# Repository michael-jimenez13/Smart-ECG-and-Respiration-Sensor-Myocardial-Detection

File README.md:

# Smart-ECG-and-Respiration-Sensor-Myocardial-Detection

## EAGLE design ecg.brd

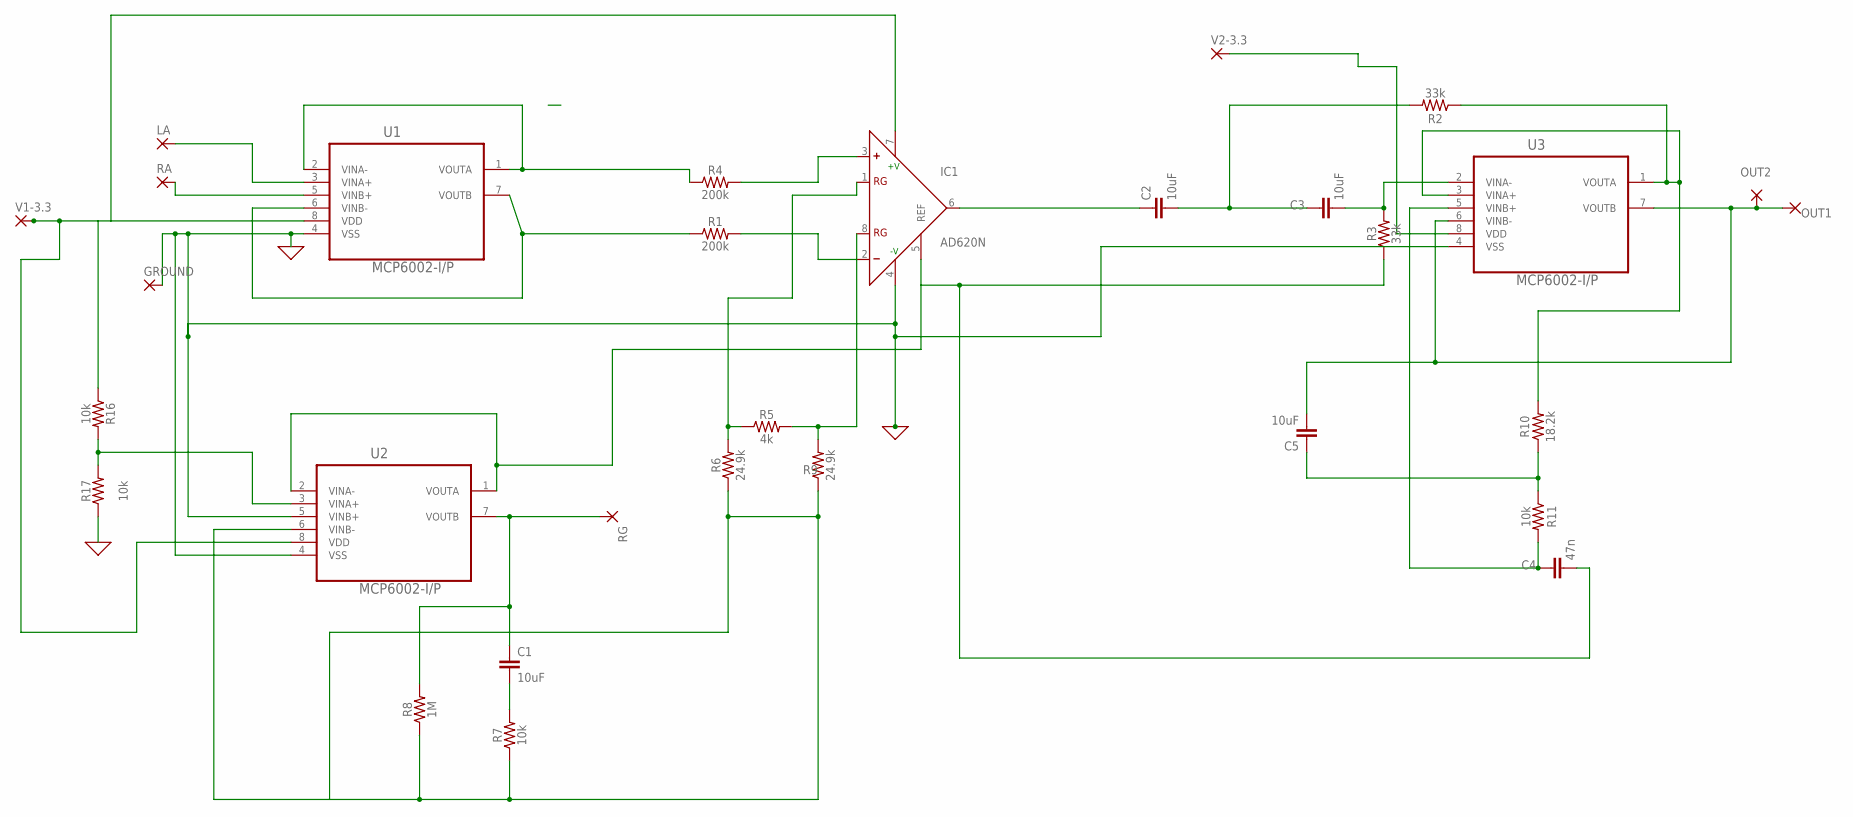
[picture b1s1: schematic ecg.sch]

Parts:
C1, C2, C3, C5: 10uF; CAP-PTH-SMALL-KIT
C4: 47n; CAP-PTH-SMALL-KIT
GROUND: 3,81/1,4
IC1: AD620N; DIL08
LA: 3,81/1,4
OUT1, OUT2: 3,81/1,4
R1, R4: 200k; AXIAL-0.3
R2, R3: 33k; AXIAL-0.3
R5: 4k; AXIAL-0.3
R6, R9: 24.9k; AXIAL-0.3
R7, R11, R16, R17: 10k; AXIAL-0.3
R8: 1M; AXIAL-0.3
R10: 18.2k; AXIAL-0.3
RA: 3,81/1,4
RG: 3,81/1,4
U1, U2, U3: MCP6002-I/P; DIP254P762X533-8
V1-3.3, V2-3.3: 3,81/1,4

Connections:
0: GROUND.1, IC1.4 (-V), R17.P$1 (1), U1.4 (VSS), U2.4 (VSS), U2.5 (VINB+), U3.4 (VSS)
unnamed: R6.P$1 (1), R7.P$1 (1), R8.P$1 (1), R9.P$1 (1), U2.6 (VINB-)
unnamed: IC1.7 (+V), R16.P$1 (1), U1.8 (VDD), U2.8 (VDD), V1-3.3.1
unnamed: C1.2, R7.P$2 (2)
unnamed: C4.2, IC1.5 (REF), R3.P$1 (1), U2.1 (VOUTA), U2.2 (VINA-)
unnamed: R16.P$2 (2), R17.P$2 (2), U2.3 (VINA+)
unnamed: R2.P$1 (1), R10.P$2 (2), U3.1 (VOUTA), U3.3 (VINA+)
unnamed: LA.1, U1.3 (VINA+)
unnamed: RA.1, U1.5 (VINB+)
unnamed: R1.P$1 (1), U1.6 (VINB-), U1.7 (VOUTB)
unnamed: R4.P$1 (1), U1.1 (VOUTA), U1.2 (VINA-)
unnamed: IC1.3 (+), R4.P$2 (2)
unnamed: U3.8 (VDD), V2-3.3.1
unnamed: C2.2, C3.1, R2.P$2 (2)
unnamed: C2.1, IC1.6 (OUT)
unnamed: C3.2, R3.P$2 (2), U3.2 (VINA-)
unnamed: C5.1, R10.P$1 (1), R11.P$1 (1)
unnamed: C4.1, R11.P$2 (2), U3.5 (VINB+)
unnamed: C5.2, OUT1.1, OUT2.1, U3.6 (VINB-), U3.7 (VOUTB)
unnamed: IC1.2 (-), R1.P$2 (2)
unnamed: C1.1, R8.P$2 (2), RG.1, U2.7 (VOUTB)
unnamed: IC1.1 (RG), R5.P$1 (1), R6.P$2 (2)
unnamed: IC1.8 (RG), R5.P$2 (2), R9.P$2 (2)

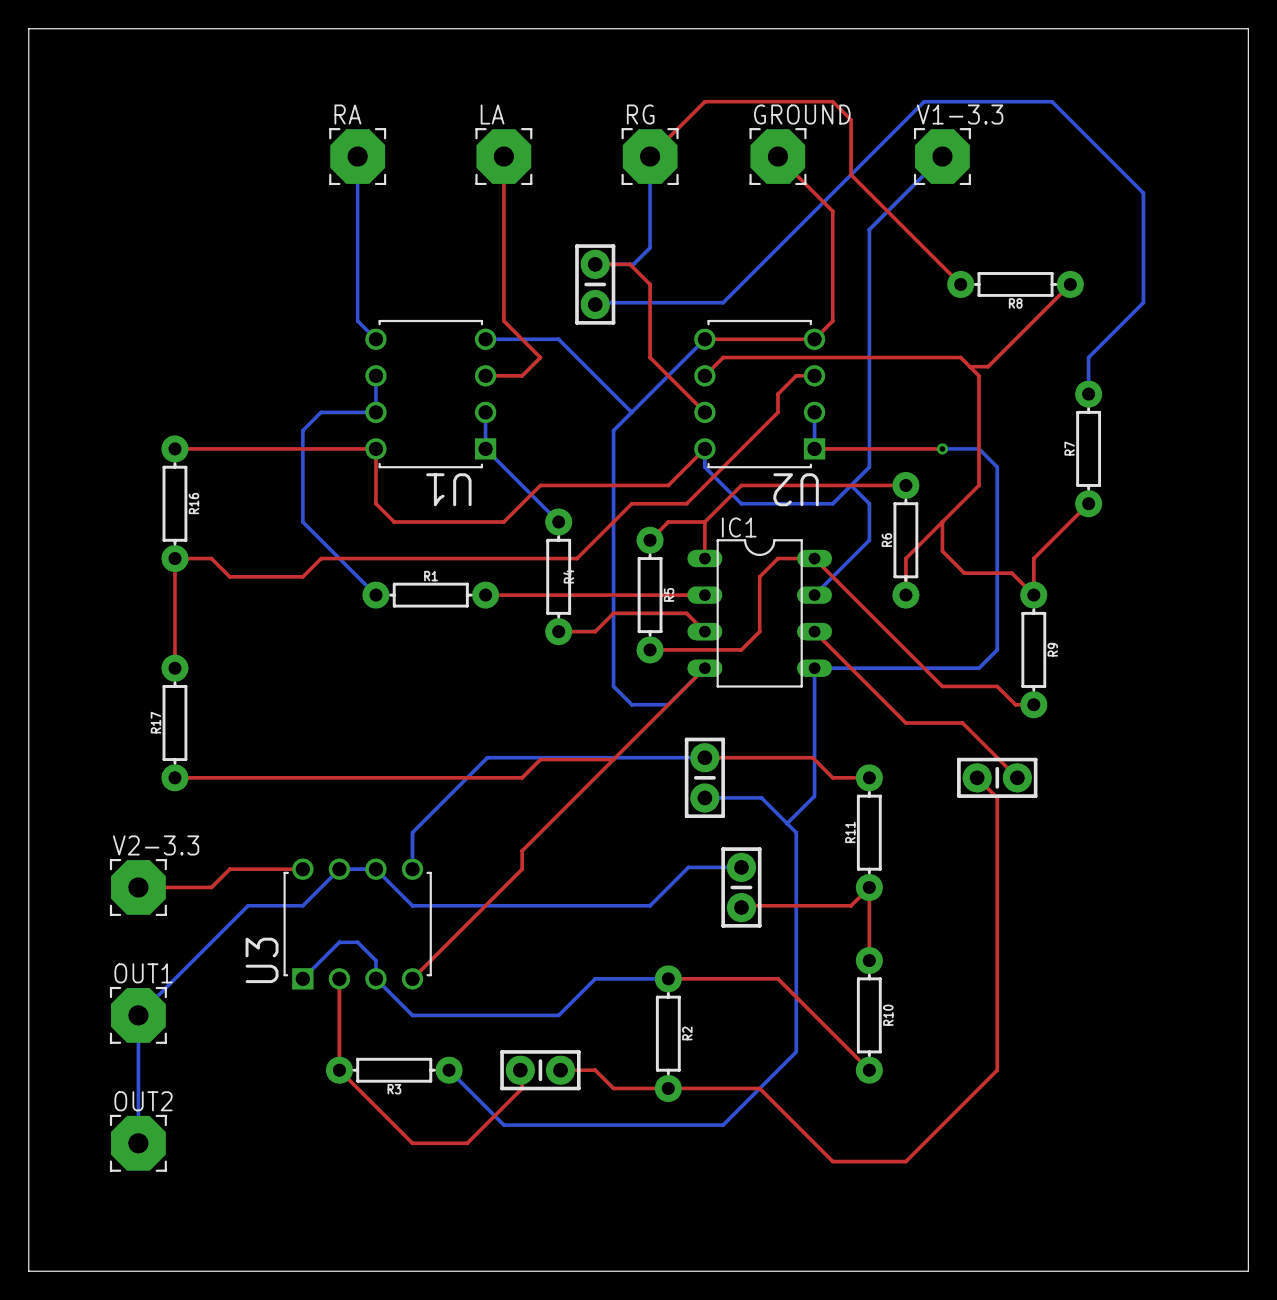
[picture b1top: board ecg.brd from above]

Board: 2 copper layers, 84.8 x 86.4 mm, 30 parts (0 on the bottom side), 23 nets.

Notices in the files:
parts and their libraries:
SparkFun-Capacitors: Licensing: Creative Commons ShareAlike 4.0 International - https://creativecommons.org/licenses/by-sa/4.0
